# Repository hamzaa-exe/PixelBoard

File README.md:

# PixelBoard

### 16×16 WS2812B RGB LED Matrix powered by WLED

PixelBoard is a custom 16×16 RGB LED matrix project using **256 individually addressable WS2812B LEDs** and a custom-designed PCB.

The custom PCB is designed specifically for PixelBoard and provides the ESP32-based controller, USB-C programming, 5V LED power distribution, level-shifted LED data, and a single 3-pin JST output for connecting the LED matrix.

The project uses **WLED** for wireless LED control, allowing the matrix to display animations, colors, effects, 2D patterns, and audio-reactive effects.

## Features

* 16×16 LED matrix
* 256 individually addressable WS2812B LEDs
* Custom ESP32-based controller PCB
* WLED firmware
* Wi-Fi control
* USB-C programming and power input
* 5V LED power output
* 5V logic-level shifting for LED data
* Single 3-pin JST LED matrix connector
* 2D matrix effects
* Audio-reactive effects
* Serpentine LED layout
* Custom enclosure and diffuser

## Hardware

| Component                              | Quantity |
| -------------------------------------- | -------: |
| Flexible 16×16 NeoPixel RGB LED Matrix |        1 |
| Custom PixelBoard Controller PCB       |        1 |
| ESP32-WROOM-32                         |        1 |
| 74AHCT125 Logic Level Shifter          |        1 |
| CH340C USB-to-Serial Converter         |        1 |
| AP2112K-3.3 Voltage Regulator          |        1 |
| LED Diffusion Acrylic                  |        1 |
| JST PH 3-Pin Cable                     |        1 |
| M2.5 Screws & Standoffs                |    1 set |
| 5V 2A Power Supply                     |        1 |
| USB-C Cable                            |        1 |

See [`bom.csv`](bom.csv) for the complete Bill of Materials, part numbers, prices, and product links.

## Custom PCB

PixelBoard uses a **custom-designed 2-layer PCB** instead of the Adafruit Sparkle Motion controller.

The PCB integrates the main electronics required to operate the LED matrix:

* ESP32-WROOM-32 controller
* CH340C USB-to-serial interface
* AP2112K 3.3V regulator
* 74AHCT125 5V logic-level shifter
* USB-C connector
* BOOT and RESET buttons
* 2A resettable fuse
* LED power filtering
* Single 3-pin JST LED output

The PCB is designed to fit within approximately **33 × 45 mm**.

## Wiring

The LED matrix connects directly to the custom PCB through the single 3-pin JST output.

```text
Custom PixelBoard PCB
        |
        | +5V  ------------> LED Matrix 5V
        |
        | GND  ------------> LED Matrix GND
        |
        | DATA ------------> LED Matrix DIN
```

The PCB uses a **74AHCT125** to shift the ESP32's 3.3V data signal to a 5V logic-level signal for the WS2812B matrix.

The LED data path is:

```text
ESP32 GPIO21
      |
      v
74AHCT125
      |
      v
330Ω Series Resistor
      |
      v
JST DATA
      |
      v
LED Matrix DIN
```

## Firmware

PixelBoard uses **WLED** rather than custom firmware.

WLED provides:

* Wireless control
* Color and brightness control
* LED effects
* 2D matrix effects
* Presets and playlists
* Audio-reactive effects

WLED can be installed using the official installer:

https://install.wled.me/

For complete installation instructions and PixelBoard-specific settings, see:

**[Firmware Documentation](Firmware/README.md)**

Detailed LED and 2D matrix configuration is available in:

**[WLED Configuration](Firmware/WLED Configuration.md)**

### Main WLED Settings

| Setting     | Value                 |
| ----------- | --------------------- |
| Controller  | Custom PixelBoard PCB |
| LED Type    | WS281x / WS2812B      |
| LED Count   | 256                   |
| Color Order | GRB                   |
| Data GPIO   | 21                    |
| Matrix      | 16 × 16               |
| First LED   | Bottom Left           |
| Orientation | Horizontal            |
| Serpentine  | ON                    |

## 2D Matrix

The matrix uses a serpentine layout with the first LED positioned at the bottom-left.

```text
→ → → → → → → → → → → → → → → →
← ← ← ← ← ← ← ← ← ← ← ← ← ← ← ←
→ → → → → → → → → → → → → → → →
← ← ← ← ← ← ← ← ← ← ← ← ← ← ← ←
```

This configuration allows WLED's 2D effects to display correctly across the entire matrix.

## Power

The LED matrix is powered from a **5V 2A power supply** connected to the custom PCB.

The PCB separates the LED power path from the ESP32's 3.3V supply using an onboard **AP2112K-3.3 regulator** and includes a **2A resettable fuse** on the LED power path.

A large bulk capacitor is also placed near the LED output to help reduce voltage fluctuations caused by rapid changes in LED current.

The 256 LEDs can draw significant current at high brightness. For this reason, WLED's brightness and current limiting should be configured appropriately.

Do not operate the complete matrix at unrestricted full-white brightness from a 5V 2A supply.

## PCB Design

The custom PCB was designed in **KiCad**.

### PCB Specifications

| Specification         | Value                    |
| --------------------- | ------------------------ |
| PCB Type              | Custom 2-layer PCB       |
| Board Size            | Approximately 33 × 45 mm |
| Controller            | ESP32-WROOM-32           |
| LED Data GPIO         | GPIO21                   |
| Logic Level           | 5V LED data              |
| LED Output            | 3-pin JST                |
| LED Supply            | 5V                       |
| Main LED Power Trace  | 1.5 mm                   |
| Standard Signal Trace | 0.5 mm                   |
| Ground                | F.Cu + B.Cu copper pours |
| USB                   | USB-C                    |

The PCB files, schematic, and manufacturing files are located in the `hardware` directory.

## Repository Structure

```text
PixelBoard/
├── README.md
├── bom.csv
├── hardware/
│   ├── schematic/
│   ├── pcb/
│   └── gerbers/
├── firmware/
│   ├── README.md
│   └── WLED Configuration.md
├── enclosure/
└── images/
```

## Resources

* [WLED Installer](https://install.wled.me/)
* [WLED Documentation](https://kno.wled.ge/)
* [16×16 NeoPixel Matrix](https://www.adafruit.com/product/2547)

## License

This project is open-source. See the `LICENSE` file for details.

---

**PixelBoard — 16×16 pixels, 256 LEDs, powered by a custom PCB and WLED.**

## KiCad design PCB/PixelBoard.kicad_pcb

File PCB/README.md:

This folder contains all the PCB files

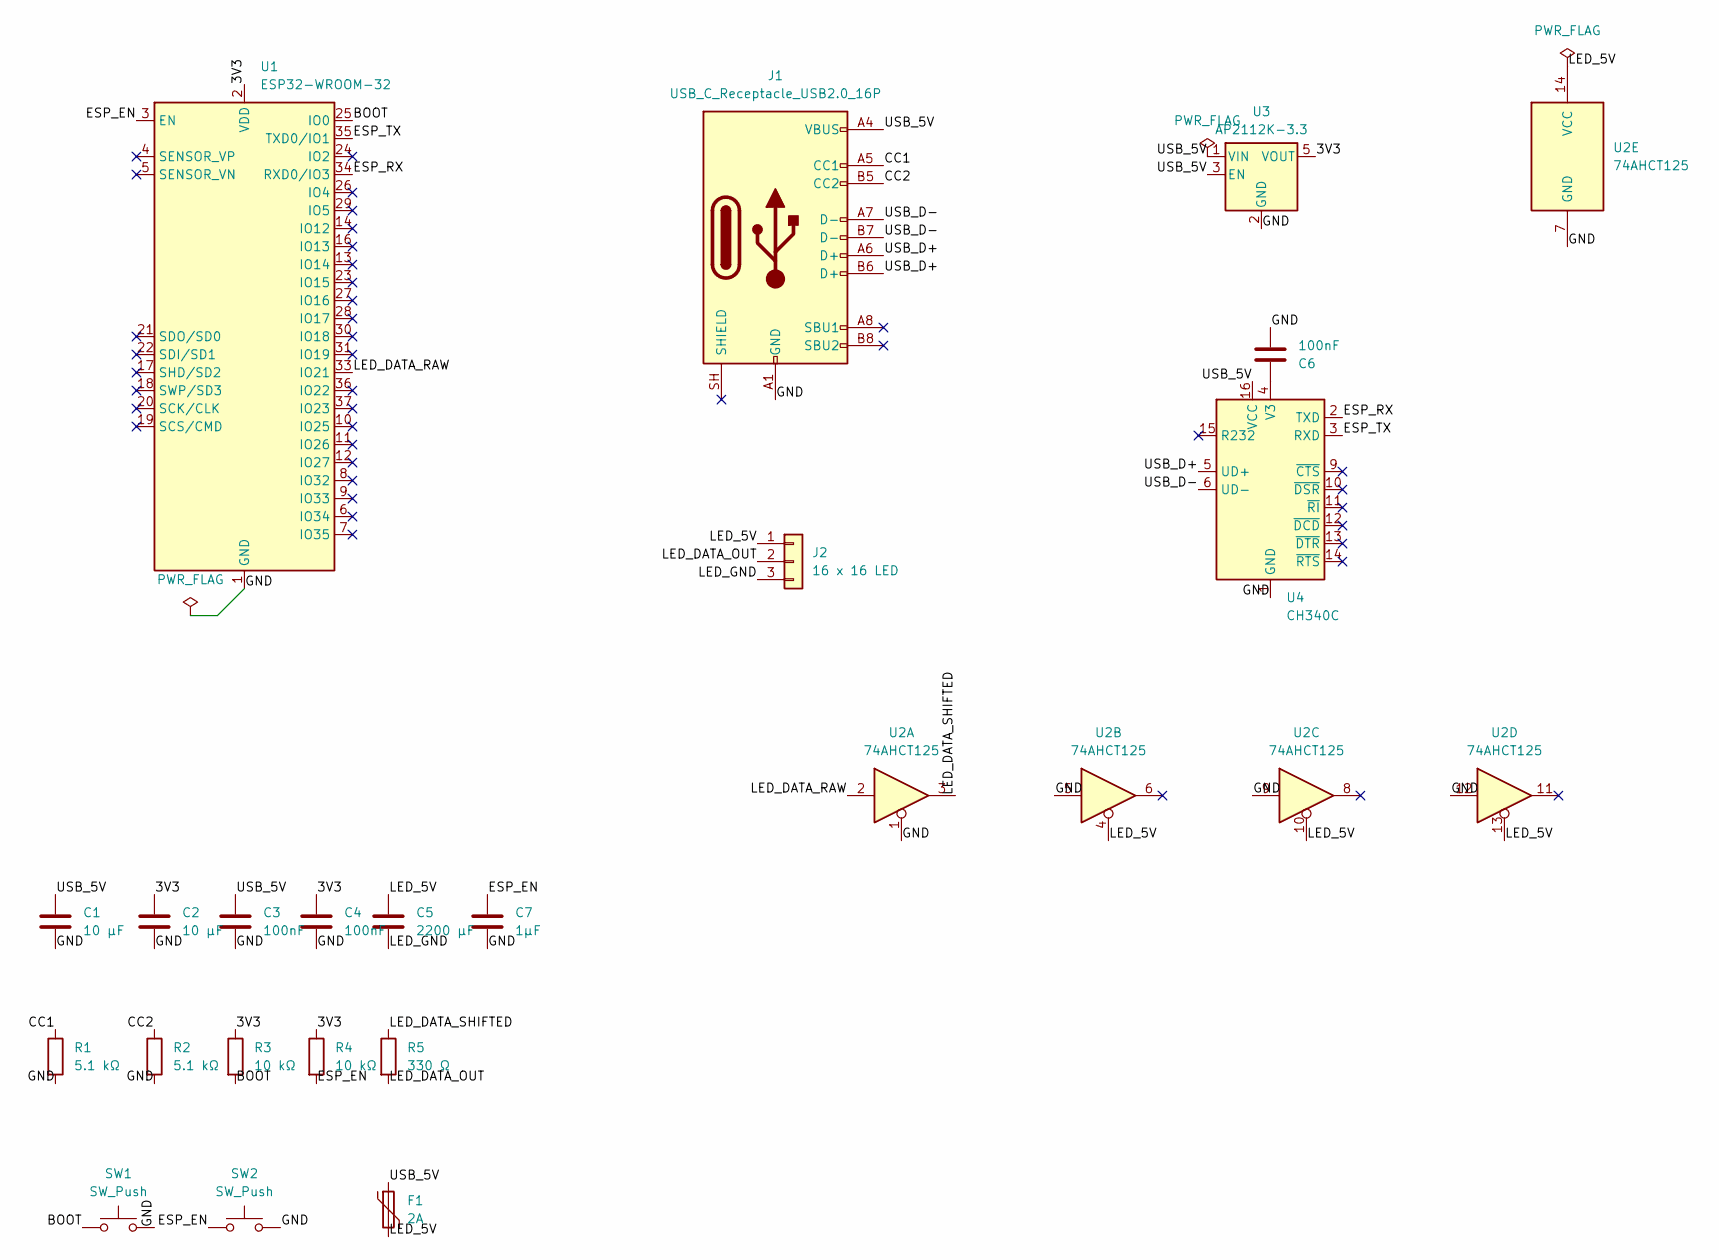
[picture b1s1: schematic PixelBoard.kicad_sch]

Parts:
C1, C2: 10 µF; C_0805_2012Metric
C3, C4, C6: 100nF; C_0805_2012Metric
C5: 2200 µF; CP_Radial_D8.0mm_P3.50mm
C7: 1µF; C_0805_2012Metric
F1: 2A; Fuse_1206_3216Metric
J1: USB_C_Receptacle_USB2.0_16P; USB_C_Receptacle_HRO_TYPE-C-31-M-12
J2: 16 x 16 LED; JST_PH_B3B-PH-K_1x03_P2.00mm_Vertical
R1, R2: 5.1 kΩ; R_0805_2012Metric
R3, R4: 10 kΩ; R_0805_2012Metric
R5: 330 Ω; R_0805_2012Metric
SW1, SW2: SW_Push; SW_SPST_TL3305A
U1: ESP32-WROOM-32
U2: 74AHCT125; SOIC-14_3.9x8.7mm_P1.27mm
U3: AP2112K-3.3; SOT-23-5
U4: CH340C; SOIC-16_3.9x9.9mm_P1.27mm

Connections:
/3V3: C2.1, C4.1, R3.1, R4.1, U1.2 (VDD), U3.5 (VOUT)
/BOOT: R3.2, SW1.1, U1.25 (IO0)
/CC1: J1.A5 (CC1), R1.1
/CC2: J1.B5 (CC2), R2.1
/ESP_EN: C7.1, R4.2, SW2.1, U1.3 (EN)
/ESP_RX: U1.34 (RXD0/IO3), U4.2 (TXD)
/ESP_TX: U1.35 (TXD0/IO1), U4.3 (RXD)
/GND: C1.2, C2.2, C3.2, C4.2, C6.2, C7.2, J1.A1 (GND), J1.A12 (GND), J1.B1 (GND), J1.B12 (GND), R1.2, R2.2, SW1.2, SW2.2, U1.1 (GND), U1.15 (GND), U1.38 (GND), U1.39 (GND), U2.1, U2.5, U2.7 (GND), U2.9, U2.12, U3.2 (GND), U4.1 (GND)
/LED_5V: C5.1, F1.2, J2.1, U2.4, U2.10, U2.13, U2.14 (VCC)
/LED_DATA_OUT: J2.2, R5.2
/LED_DATA_RAW: U1.33 (IO21), U2.2
/LED_DATA_SHIFTED: R5.1, U2.3
/LED_GND: C5.2, J2.3
/USB_5V: C1.1, C3.1, F1.1, J1.A4 (VBUS), J1.A9 (VBUS), J1.B4 (VBUS), J1.B9 (VBUS), U3.1 (VIN), U3.3 (EN), U4.16 (VCC)
/USB_D+: J1.A6 (D+), J1.B6 (D+), U4.5 (UD+)
/USB_D-: J1.A7 (D-), J1.B7 (D-), U4.6 (UD-)
unnamed: C6.1, U4.4 (V3)

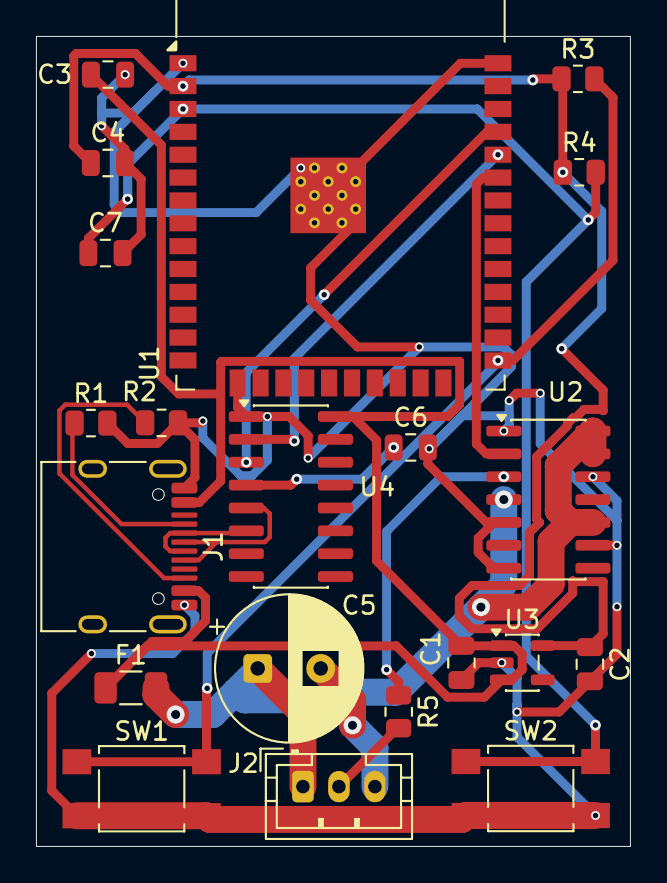
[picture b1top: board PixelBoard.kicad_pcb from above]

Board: 2 copper layers, 33.0 x 45.0 mm, 21 parts (0 on the bottom side), 17 nets.
